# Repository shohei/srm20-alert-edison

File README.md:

/etc/systemd/system/srm20.service
```
[Unit]
Description=srm20 service
After=mdns.service pm2.service

[Service]
ExecStart=/bin/su root -c 'cd /home/root/srm20 && pm2 start app.js'
Restart=always
RestartSec=10s

[Install]
WantedBy=default.target

```

```
$ systemctl enable srm20
$ systemctl start srm20
```

#install pm2
```
npm install -g pm2
pm2 startup
pm2 startup systemd
```

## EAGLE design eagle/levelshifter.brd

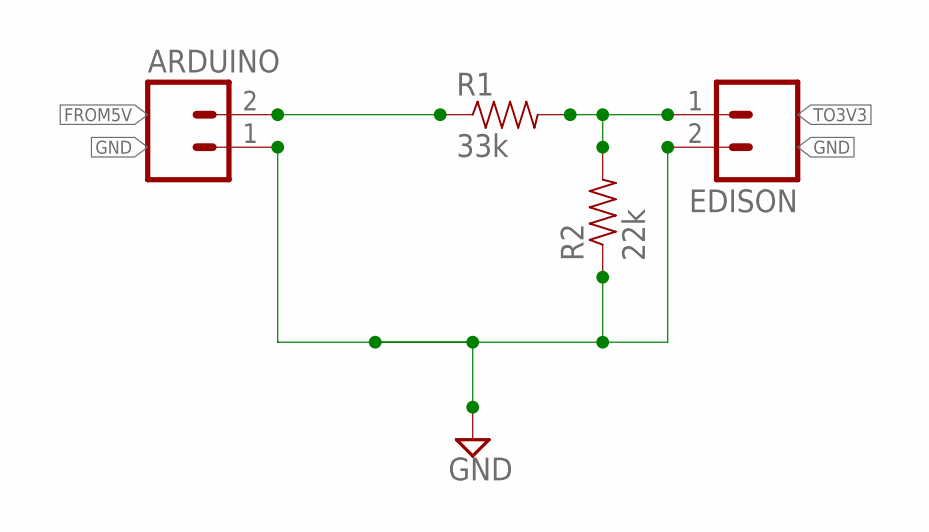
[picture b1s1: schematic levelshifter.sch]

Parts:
ARDUINO: M02PTH3; 1X02_LONGPADS
EDISON: M02PTH3; 1X02_LONGPADS
R1: 33k; AXIAL-0.3
R2: 22k; AXIAL-0.3

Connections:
FROM5V: ARDUINO.2, R1.P$1 (1)
GND: ARDUINO.1, EDISON.2, R2.P$1 (1)
TO3V3: EDISON.1, R1.P$2 (2), R2.P$2 (2)

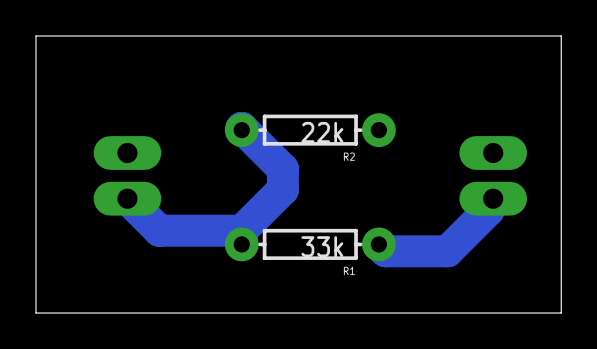
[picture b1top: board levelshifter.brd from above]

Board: 2 copper layers, 29.2 x 15.4 mm, 4 parts (0 on the bottom side), 3 nets.

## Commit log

2016-02-23 add server
2016-02-23 change
2016-02-23 add config for pulldown
2016-02-23 add readme
2016-02-23 change channel name and add eagle files

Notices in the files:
parts and their libraries:
SparkFun: Licensing: CC v3.0 Share-Alike You are welcome to use this library for commercial purposes.
